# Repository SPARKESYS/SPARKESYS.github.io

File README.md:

<body>

<h1 align="center" >About</h1>

<h2  align="center"  id="computer--electrical-engineer"> COMPUTER &amp; ELECTRICAL ENGINEER</h2>

<p align="center" >This is a site dedicated to my Portfolio and Project Showcase</p>
<p align="center">Hi, My name is Jarrod Resmondo. I am a professional computer and electrical engineer with a passion for developing robotics, designing circuitry and printed circuit boards, programming automation sequences and custom controllers</p>
<p align="center">I am also a mechanic, welder, fabricator and home renovator</p>

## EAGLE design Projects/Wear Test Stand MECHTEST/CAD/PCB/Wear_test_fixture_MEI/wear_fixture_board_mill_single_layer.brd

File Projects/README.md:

## - - - - - - - - - - - - - - - - - - - - - - - - - - - - - - - - - - - - - - 
## -------------------------------------------------------------------------- 
## ---- PROJECTS ------------------------- 
## -------------------------------------------------------------------------- 
## -------------------------------------------------------------------------- 
## ------------------------------------------------- 
## ----------------------------------------------- 
## ---------------------------------------------------- 

### -[CV]()

### -[Education]()

### -[Projects](https://github.com/SPARKESYS/SPARKESYS.github.io/tree/main/Projects)

You can use the [editor on GitHub](https://github.com/SPARKESYS/SPARKESYS.github.io/edit/main/README.md) to maintain and preview the content for your website in Markdown files.

Whenever you commit to this repository, GitHub Pages will run [Jekyll](https://jekyllrb.com/) to rebuild the pages in your site, from the content in your Markdown files.

### Markdown

Markdown is a lightweight and easy-to-use syntax for styling your writing. It includes conventions for

```markdown
Syntax highlighted code block

# Header 1
Jarrod Resmondo
## Header 2
University Of West Florida 
Computer Engineering 
Electrical Engineering
Computer Science
### Header 3

-[LINK](CV)
-Education
-Projects

**Bold** and _Italic_ and `Code` text

[Link](url) and 
```

For more details see [Basic writing and formatting syntax](https://docs.github.com/en/github/writing-on-github/getting-started-with-writing-and-formatting-on-github/basic-writing-and-formatting-syntax).

### Jekyll Themes

Your Pages site will use the layout and styles from the Jekyll theme you have selected in your [repository settings](https://github.com/SPARKESYS/SPARKESYS.github.io/settings/pages). The name of this theme is saved in the Jekyll `_config.yml` configuration file.

### Support or Contact

Having trouble with Pages? Check out our [documentation](https://docs.github.com/categories/github-pages-basics/) or [contact support](https://support.github.com/contact) and we’ll help you sort it out.

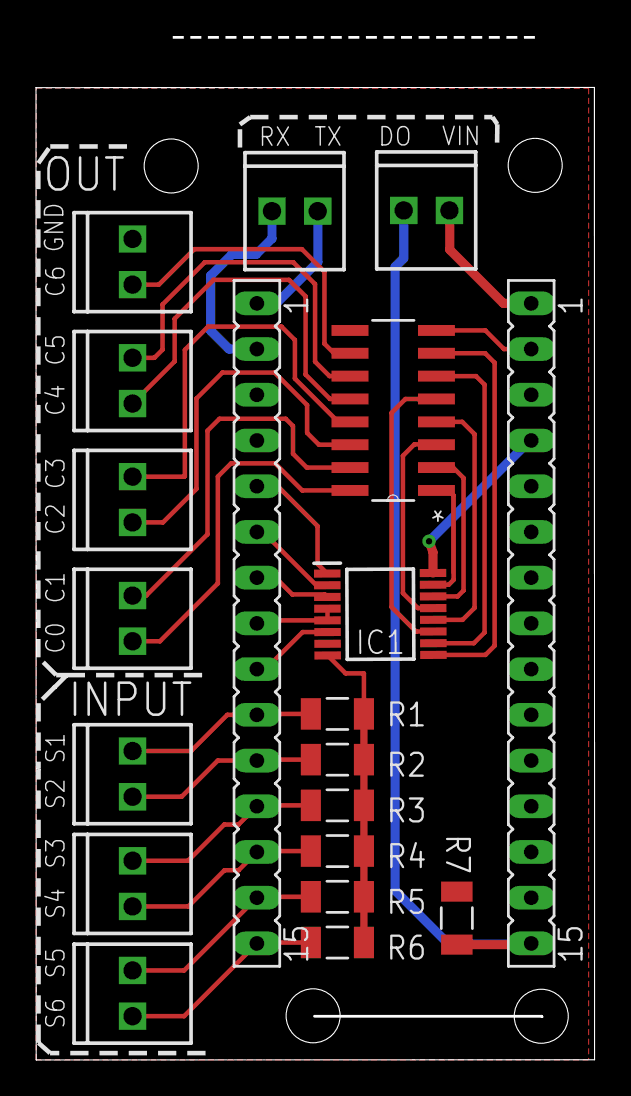
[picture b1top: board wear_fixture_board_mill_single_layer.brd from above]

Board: 2 copper layers, 30.9 x 56.7 mm, 20 parts (0 on the bottom side), 31 nets.

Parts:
IC1: 74VHC238FT; SOP65P640X120-16N
J1, J2, J3, J4, J5, J6, J7, J8, J9: 1X02_2.54_SCREWTERM
R1, R2, R3, R4, R5, R6, R7: RESC3216X71N
SV1, SV2: FE15
U1: ULN2003ADR; SOIC127P600X175-16N

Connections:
DEWE_: J7.P2, R7.2, SV1.15
EN: IC1.4, IC1.5, SV2.8
GND: IC1.8, J8.P1, R1.2, R2.2, R3.2, R4.2, R5.2, R6.2, R7.1, SV1.2, SV2.4, U1.8
IN_0: IC1.6, SV2.9
OUT1: J4.P2, U1.16
OUT2: J4.P1, U1.15
OUT3: J5.P2, U1.14
OUT4: J5.P1, U1.13
OUT5: J6.P2, U1.12
OUT6: J6.P1, U1.11
OUT7: J8.P2, U1.10
RX: J9.P2, SV2.2
SEL_A: IC1.1, SV2.5
SEL_B: IC1.2, SV2.6
SEL_C: IC1.3, SV2.7
SNS1: J1.P1, R1.1, SV2.10
SNS2: J1.P2, R2.1, SV2.11
SNS3: J2.P1, R3.1, SV2.12
SNS4: J2.P2, R4.1, SV2.13
SNS5: J3.P1, R5.1, SV2.14
SNS6: J3.P2, R6.1, SV2.15
TX: J9.P1, SV2.1
VCC: IC1.16, SV1.4
VIN: J7.P1, SV1.1
Y0: IC1.15, U1.1
Y1: IC1.14, U1.2
Y2: IC1.13, U1.3
Y3: IC1.12, U1.4
Y4: IC1.11, U1.5
Y5: IC1.10, U1.6
Y6: IC1.9, U1.7

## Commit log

2022-06-24 Set theme jekyll-theme-hacker
2022-06-24 Project Files Added
2022-06-24 Building Site
    added education and cv folders and config files to folders
2022-06-24 Building Site
    ADD README TO PROJECTS FOLDER
2022-06-24 Building Site
    Projects page
2022-06-24 update Projects URL
2022-06-24 Building Site
2022-06-24 Building Site
    Update pages
2022-06-24 Building site
    UPDATED LINKS
2022-06-24 removed files
2022-06-24 Setting up Mutoscope
2022-06-24 upload images
2022-06-25 upload documents
2022-06-25 images added
2022-06-26 build jekyll locally
2022-06-26 site building
2022-06-26 building the site
2022-06-29 images of projects
2022-06-29 images for site
2022-07-01 site building resize images
2022-07-06 building website
2022-07-07 fixing images extensions
2022-07-07 image extensions
2022-07-26 cv to resume
2022-08-10 updating ROV
2022-08-10 UROV Details
2022-08-10 updating urov
2022-08-10 details
2022-08-30 added ptg governor

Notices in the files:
parts and their libraries:
SparkFun-Connectors: Licensing: Creative Commons ShareAlike 4.0 International - https://creativecommons.org/licenses/by-sa/4.0
